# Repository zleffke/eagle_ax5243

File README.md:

# eagle_ax5243
EagleCAD AX5243 projects.

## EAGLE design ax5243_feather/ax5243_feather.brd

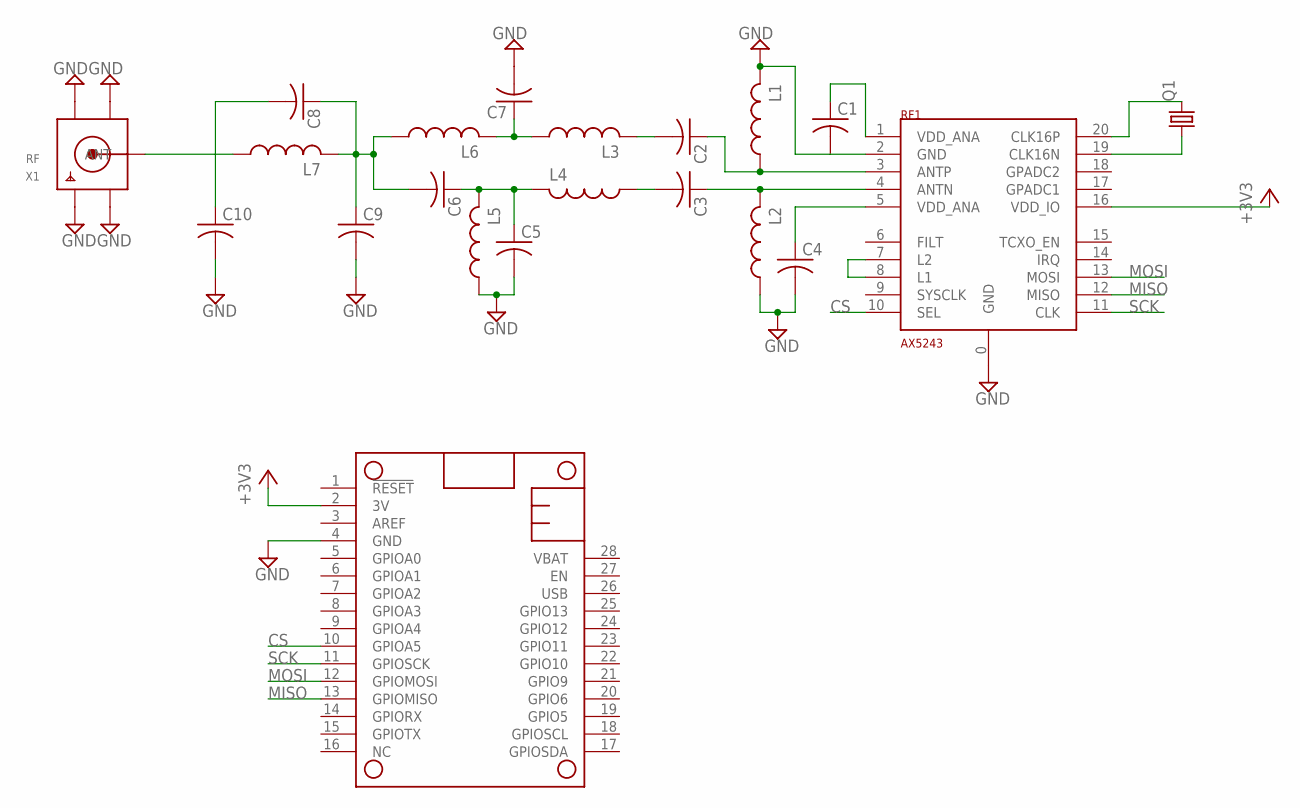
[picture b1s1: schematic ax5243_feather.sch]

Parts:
C1, C2, C3, C4, C5, C6, C7, C8, C9, C10: C-USC0805K; C0805K
L1, L2, L3, L4, L5, L6, L7: L-US0805K; C0805K
MS1: FEATHERWING
Q1: CRYSTALCTS406; CTS406
RF1: AX5243; QFN20-4X4MM
X1: RF; SMA_EDGELAUNCH_UFL

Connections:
+3V3: MS1.2 (3V), RF1.16 (VDD_IO)
ANTN: C3.1, L2.2, RF1.4 (ANTN)
ANTP: C2.1, L1.1, RF1.3 (ANTP)
CS: MS1.10 (GPIOA5), RF1.10 (SEL)
GND: C1.2, C4.2, C5.2, C7.2, C9.2, C10.2, L1.2, L2.1, L5.1, MS1.4 (GND), RF1.0 (GND), RF1.2 (GND), X1.GND@1 (GND1), X1.GND@2 (GND2), X1.GND@3 (GND3), X1.GND@4 (GND4)
MISO: MS1.13 (GPIOMISO), RF1.12 (MISO)
MOSI: MS1.12 (GPIOMOSI), RF1.13 (MOSI)
unnamed: RF1.7 (L2), RF1.8 (L1)
unnamed: C4.1, RF1.5 (VDD_ANA)
unnamed: C1.1, RF1.1 (VDD_ANA)
unnamed: Q1.3 (2), RF1.20 (CLK16P)
unnamed: C3.2, L4.1
unnamed: C2.2, L3.2
unnamed: C5.1, C6.1, L4.2, L5.2
unnamed: Q1.1, RF1.19 (CLK16N)
unnamed: C6.2, C8.1, C9.1, L6.1, L7.2
unnamed: C7.1, L3.1, L6.2
unnamed: C8.2, C10.1, L7.1, X1.P (ANT)
SCK: MS1.11 (GPIOSCK), RF1.11 (CLK)

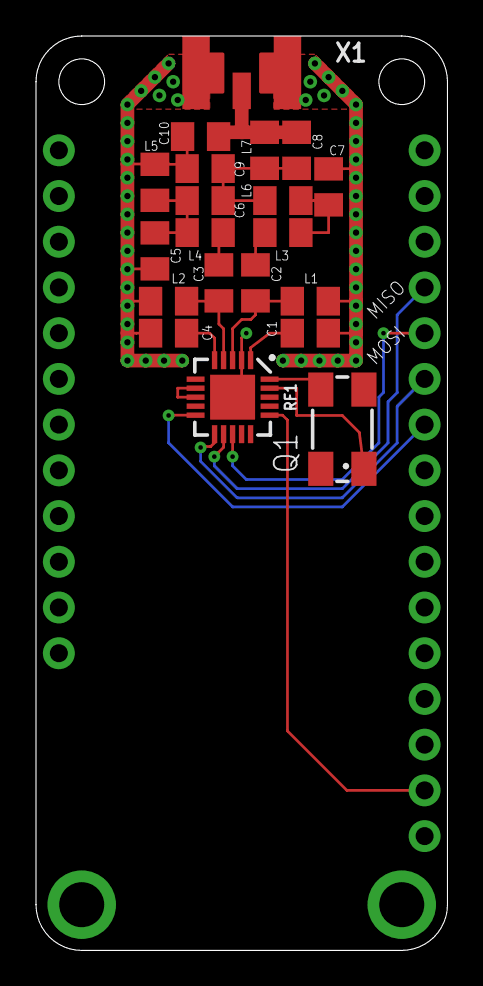
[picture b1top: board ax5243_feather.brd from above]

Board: 2 copper layers, 22.9 x 50.8 mm, 21 parts (0 on the bottom side), 19 nets.

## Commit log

2018-09-01 initial copy from obsolete repo
